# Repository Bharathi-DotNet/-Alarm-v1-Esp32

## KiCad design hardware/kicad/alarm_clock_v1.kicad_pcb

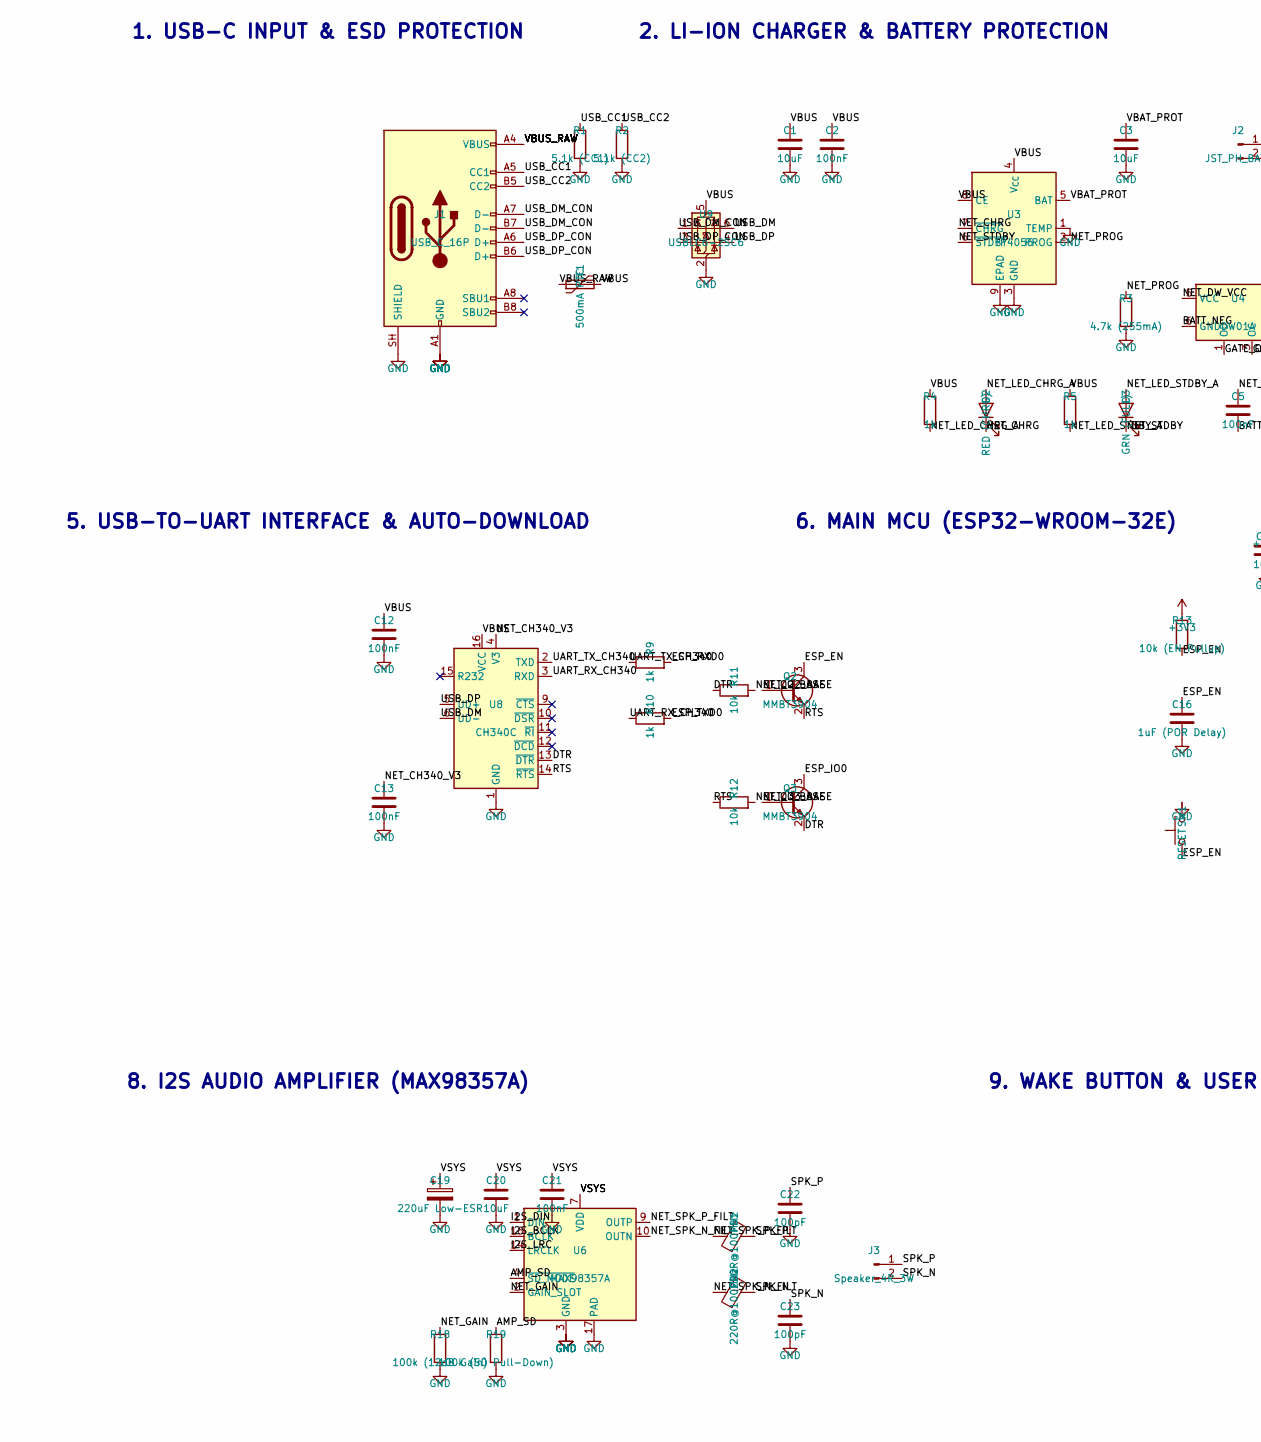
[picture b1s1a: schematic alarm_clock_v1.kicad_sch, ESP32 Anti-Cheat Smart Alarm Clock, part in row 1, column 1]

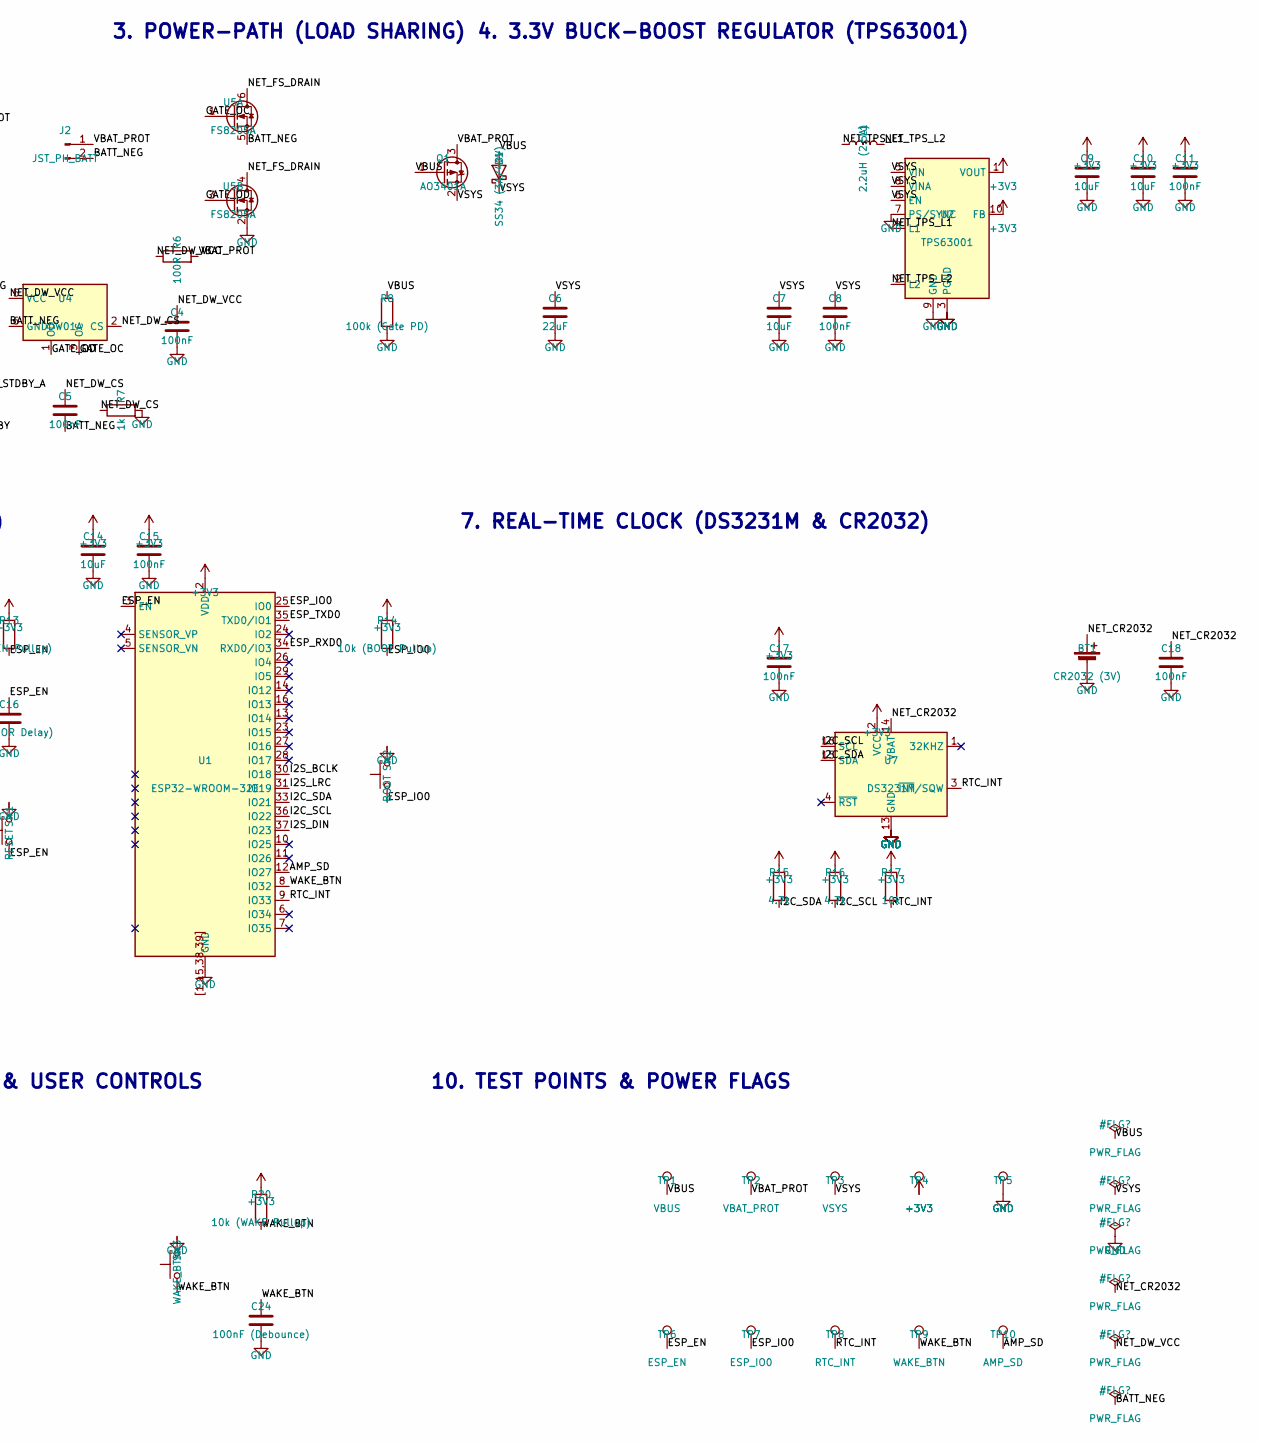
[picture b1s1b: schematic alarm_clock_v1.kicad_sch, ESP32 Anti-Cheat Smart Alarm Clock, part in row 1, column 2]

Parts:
BT1: CR2032 (3V); BatteryHolder_Keystone_1060_1x2032
C1, C3, C7, C9, C10, C14, C20: 10uF; C_0805_2012Metric
C2, C4, C5, C8, C11, C12, C13, C15, C17, C18, C21: 100nF; C_0603_1608Metric
C6: 22uF; C_0805_2012Metric
C16: 1uF (POR Delay); C_0603_1608Metric
C19: 220uF Low-ESR; CP_EIA-7343-31_Kemet-D
C22, C23: 100pF; C_0603_1608Metric
C24: 100nF (Debounce); C_0603_1608Metric
D1: SS34 (3A/40V); D_SOD-123
D2: RED (CHRG); LED_0603_1608Metric
D3: GRN (FULL); LED_0603_1608Metric
F1: 500mA PTC; Fuse_1812_4532Metric
FB1, FB2: 220R@100MHz; L_0603_1608Metric
J1: USB_C_16P; USB_C_Receptacle_HRO_TYPE-C-31-M-12
J2: JST_PH_BATT; JST_PH_B2B-PH-K_1x02_P2.00mm_Vertical
J3: Speaker_4R_3W; JST_PH_B2B-PH-K_1x02_P2.00mm_Vertical
L1: 2.2uH (2.5A); L_1210_3225Metric
Q1: AO3401A; SOT-23
Q2, Q3: MMBT3904; SOT-23
R1: 5.1k (CC1); R_0603_1608Metric
R2: 5.1k (CC2); R_0603_1608Metric
R3: 4.7k (255mA); R_0603_1608Metric
R4, R5, R7, R9, R10: 1k; R_0603_1608Metric
R6: 100R; R_0603_1608Metric
R8: 100k (Gate PD); R_0603_1608Metric
R11, R12, R17: 10k; R_0603_1608Metric
R13: 10k (EN Pullup); R_0603_1608Metric
R14: 10k (BOOT Pullup); R_0603_1608Metric
R15, R16: 4.7k; R_0603_1608Metric
R18: 100k (12dB Gain); R_0603_1608Metric
R19: 100k (SD Pull-Down); R_0603_1608Metric
R20: 10k (WAKE Pullup); R_0603_1608Metric
SW1: RESET; SW_Push_1TS009xxxx-xxxx-xxxx_6x6x5mm
SW2: BOOT; SW_Push_1TS009xxxx-xxxx-xxxx_6x6x5mm
SW3: WAKE_BTN; SW_Push_1TS009xxxx-xxxx-xxxx_6x6x5mm
TP1: VBUS; TestPoint_Pad_D1.0mm
TP2: VBAT_PROT; TestPoint_Pad_D1.0mm
TP3: VSYS; TestPoint_Pad_D1.0mm
TP4: +3V3; TestPoint_Pad_D1.0mm
TP5: GND; TestPoint_Pad_D1.0mm
TP6: ESP_EN; TestPoint_Pad_D1.0mm
TP7: ESP_IO0; TestPoint_Pad_D1.0mm
TP8: RTC_INT; TestPoint_Pad_D1.0mm
TP9: WAKE_BTN; TestPoint_Pad_D1.0mm
TP10: AMP_SD; TestPoint_Pad_D1.0mm
U1: ESP32-WROOM-32E
U2: TPS63001; Texas_DRC0010J_ThermalVias
U3: TP4056; SOIC-8-1EP_3.9x4.9mm_P1.27mm_EP2.41x3.3mm_ThermalVias
U4: DW01A; SOT-23-6
U5: FS8205A; TSSOP-8_4.4x3mm_P0.65mm
U6: MAX98357A; TQFN-16-1EP_3x3mm_P0.5mm_EP1.6x1.6mm
U7: DS3231M; SOIC-16W_7.5x10.3mm_P1.27mm
U8: CH340C; SOIC-16_3.9x9.9mm_P1.27mm
U9: USBLC6-2SC6; SOT-23-6

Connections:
+3V3: C9.1, C10.1, C11.1, C14.1, C15.1, C17.1, R13.1, R14.1, R15.1, R16.1, R17.1, R20.1, TP4.1, U1.2 (VDD), U2.1 (VOUT), U2.10 (FB), U7.2 (VCC)
/AMP_SD: R19.1, TP10.1, U1.12 (IO27), U6.4 (~SD_MODE)
/BATT_NEG: C5.2, J2.2, U4.6 (GND), U5.5 (S)
/DTR: Q3.2 (E), R11.1, U8.13 (~DTR)
/ESP_EN: C16.1, Q2.3 (C), R13.2, SW1.1, TP6.1, U1.3 (EN)
/ESP_IO0: Q3.3 (C), R14.2, SW2.1, TP7.1, U1.25 (IO0)
/ESP_RXD0: R9.2, U1.34 (RXD0/IO3)
/ESP_TXD0: R10.2, U1.35 (TXD0/IO1)
/GATE_OC: U4.3 (OC), U5.1 (G)
/GATE_OD: U4.1 (OD), U5.3 (G)
/I2C_SCL: R16.2, U1.36 (IO22), U7.16 (SCL)
/I2C_SDA: R15.2, U1.33 (IO21), U7.15 (SDA)
/I2S_BCLK: U1.30 (IO18), U6.16 (BCLK)
/I2S_DIN: U1.37 (IO23), U6.1 (DIN)
/I2S_LRC: U1.31 (IO19), U6.14 (LRCLK)
/NET_CH340_V3: C13.1, U8.4 (V3)
/NET_CHRG: D2.1 (K), U3.7 (~CHRG)
/NET_CR2032: BT1.1 (+), C18.1, U7.14 (VBAT)
/NET_DW_CS: C5.1, R7.1, U4.2 (CS)
/NET_DW_VCC: C4.1, R6.1, U4.5 (VCC)
/NET_FS_DRAIN: U5.4 (D), U5.6 (D)
/NET_GAIN: R18.1, U6.2 (GAIN_SLOT)
/NET_LED_CHRG_A: D2.2 (A), R4.2
/NET_LED_STDBY_A: D3.2 (A), R5.2
/NET_PROG: R3.1, U3.2 (PROG)
/NET_Q2_BASE: Q2.1 (B), R11.2
/NET_Q3_BASE: Q3.1 (B), R12.2
/NET_SPK_N_FILT: FB2.1, U6.10 (OUTN)
/NET_SPK_P_FILT: FB1.1, U6.9 (OUTP)
/NET_STDBY: D3.1 (K), U3.6 (~STDBY)
/NET_TPS_L1: L1.1, U2.4 (L1)
/NET_TPS_L2: L1.2, U2.2 (L2)
/RTC_INT: R17.2, TP8.1, U1.9 (IO33), U7.3 (~INT/SQW)
/RTS: Q2.2 (E), R12.1, U8.14 (~RTS)
/SPK_N: C23.1, FB2.2, J3.2
/SPK_P: C22.1, FB1.2, J3.1
/UART_RX_CH340: R10.1, U8.3 (RXD)
/UART_TX_CH340: R9.1, U8.2 (TXD)
/USB_CC1: J1.A5 (CC1), R1.1
/USB_CC2: J1.B5 (CC2), R2.1
/USB_DM: U8.6 (UD-), U9.6 (I/O1)
/USB_DM_CON: J1.A7 (D-), J1.B7 (D-), U9.1 (I/O1)
/USB_DP: U8.5 (UD+), U9.4 (I/O2)
/USB_DP_CON: J1.A6 (D+), J1.B6 (D+), U9.3 (I/O2)
/VBAT_PROT: C3.1, J2.1, Q1.3 (D), R6.2, TP2.1, U3.5 (BAT)
/VBUS: C1.1, C2.1, C12.1, D1.2 (A), F1.2, Q1.1 (G), R4.1, R5.1, R8.1, TP1.1, U3.4 (V_{CC}), U3.8 (CE), U8.16 (VCC), U9.5 (VBUS)
/VBUS_RAW: F1.1, J1.A4 (VBUS), J1.A9 (VBUS), J1.B4 (VBUS), J1.B9 (VBUS)
/VSYS: C6.1, C7.1, C8.1, C19.1, C20.1, C21.1, D1.1 (K), Q1.2 (S), TP3.1, U2.5 (VIN), U2.6 (EN), U2.8 (VINA), U6.7 (VDD), U6.8 (VDD)
/WAKE_BTN: C24.1, R20.2, SW3.1, TP9.1, U1.8 (IO32)
GND: BT1.2 (-), C1.2, C2.2, C3.2, C4.2, C6.2, C7.2, C8.2, C9.2, C10.2, C11.2, C12.2, C13.2, C14.2, C15.2, C16.2, C17.2, C18.2, C19.2, C20.2, C21.2, C22.2, C23.2, C24.2, J1.A1 (GND), J1.A12 (GND), J1.B1 (GND), J1.B12 (GND), J1.SH (SHIELD), R1.2, R2.2, R3.2, R7.2, R8.2, R18.2, R19.2, SW1.2, SW2.2, SW3.2, TP5.1, U1.1, U1.15, U1.38, U1.39, U1.[1,15,38,39] (GND), U2.3 (PGND), U2.7 (PS/SYNC), U2.9 (GND), U2.11 (PGND), U3.1 (TEMP), U3.3 (GND), U3.9 (EPAD), U5.2 (S), U6.3 (GND), U6.11 (GND), U6.15 (GND), U6.17 (PAD), U7.5 (GND), U7.6 (GND), U7.7 (GND), U7.8 (GND), U7.9 (GND), U7.10 (GND), U7.11 (GND), U7.12 (GND), U7.13 (GND), U8.1 (GND), U9.2 (GND)

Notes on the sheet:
1. USB-C INPUT & ESD PROTECTION
2. LI-ION CHARGER & BATTERY PROTECTION
3. POWER-PATH (LOAD SHARING)
4. 3.3V BUCK-BOOST REGULATOR (TPS63001)
5. USB-TO-UART INTERFACE & AUTO-DOWNLOAD
6. MAIN MCU (ESP32-WROOM-32E)
7. REAL-TIME CLOCK (DS3231M & CR2032)
8. I2S AUDIO AMPLIFIER (MAX98357A)
9. WAKE BUTTON & USER CONTROLS
10. TEST POINTS & POWER FLAGS

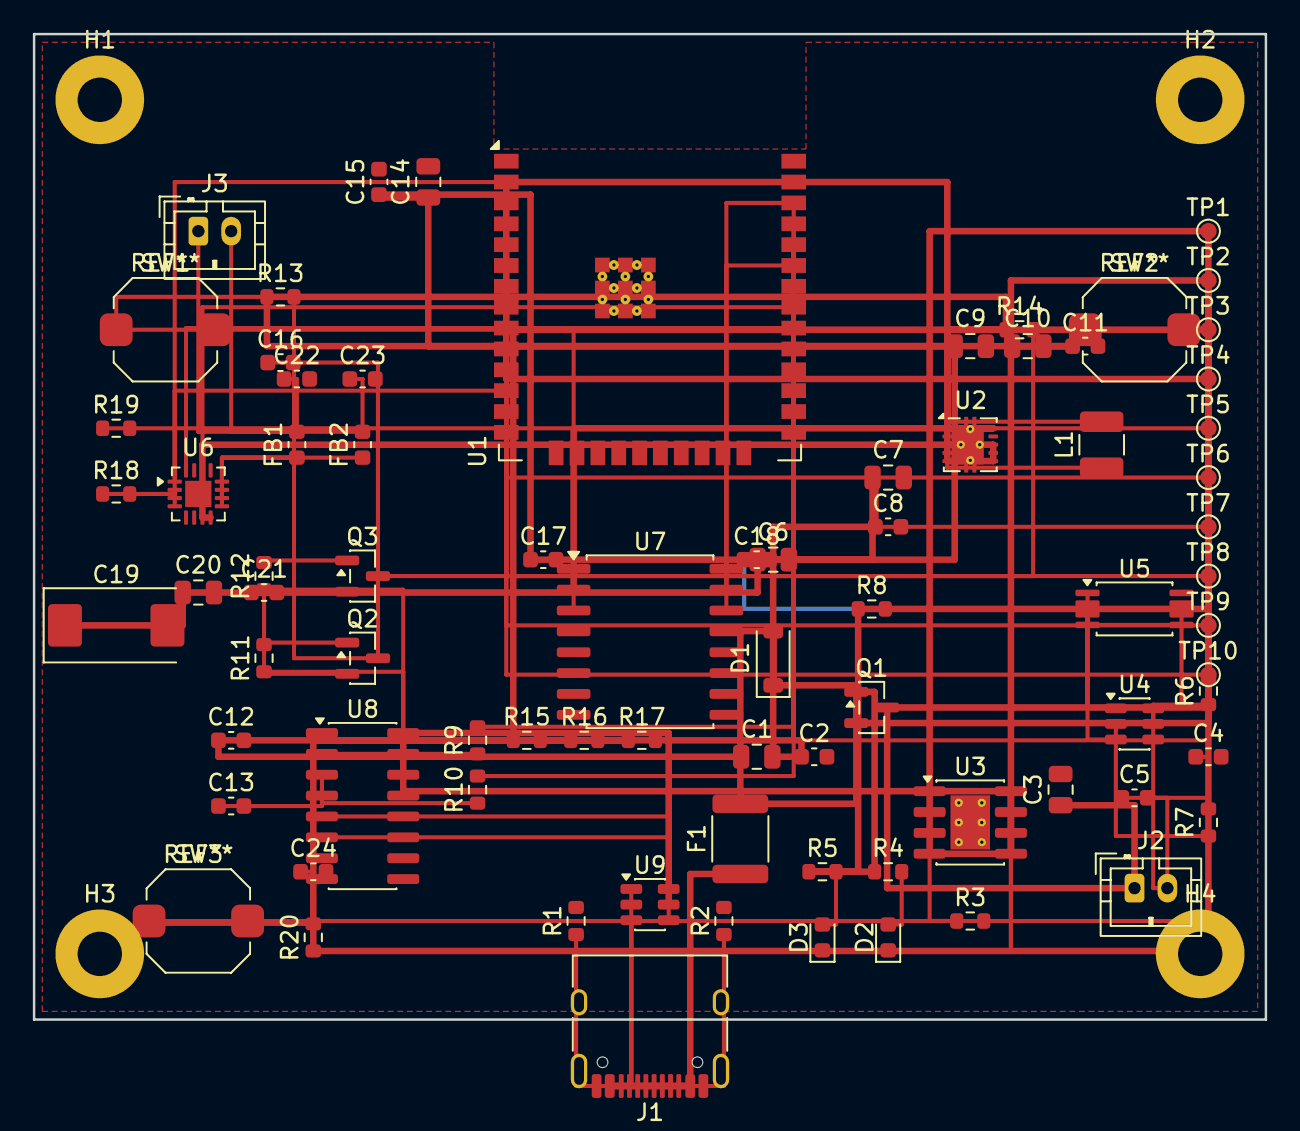
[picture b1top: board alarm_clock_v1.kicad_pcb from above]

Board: 2 copper layers, 75.0 x 60.0 mm, 84 parts (1 on the bottom side), 50 nets.

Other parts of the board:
H1, H2, H3, H4: MountingHole_2.7mm_M2.5_Pad

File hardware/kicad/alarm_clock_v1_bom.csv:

"Refs","Value","Footprint","Qty","DNP"
"BT1","CR2032 (3V)","Battery:BatteryHolder_Keystone_1060_1x2032","1",""
"C1","10uF","Capacitor_SMD:C_0805_2012Metric","1",""
"C2","100nF","Capacitor_SMD:C_0603_1608Metric","1",""
"C3","10uF","Capacitor_SMD:C_0805_2012Metric","1",""
"C4","100nF","Capacitor_SMD:C_0603_1608Metric","1",""
"C5","100nF","Capacitor_SMD:C_0603_1608Metric","1",""
"C6","22uF","Capacitor_SMD:C_0805_2012Metric","1",""
"C7","10uF","Capacitor_SMD:C_0805_2012Metric","1",""
"C8","100nF","Capacitor_SMD:C_0603_1608Metric","1",""
"C9","10uF","Capacitor_SMD:C_0805_2012Metric","1",""
"C10","10uF","Capacitor_SMD:C_0805_2012Metric","1",""
"C11","100nF","Capacitor_SMD:C_0603_1608Metric","1",""
"C12","100nF","Capacitor_SMD:C_0603_1608Metric","1",""
"C13","100nF","Capacitor_SMD:C_0603_1608Metric","1",""
"C14","10uF","Capacitor_SMD:C_0805_2012Metric","1",""
"C15","100nF","Capacitor_SMD:C_0603_1608Metric","1",""
"C16","1uF (POR Delay)","Capacitor_SMD:C_0603_1608Metric","1",""
"C17","100nF","Capacitor_SMD:C_0603_1608Metric","1",""
"C18","100nF","Capacitor_SMD:C_0603_1608Metric","1",""
"C19","220uF Low-ESR","Capacitor_Tantalum_SMD:CP_EIA-7343-31_Kemet-D","1",""
"C20","10uF","Capacitor_SMD:C_0805_2012Metric","1",""
"C21","100nF","Capacitor_SMD:C_0603_1608Metric","1",""
"C22","100pF","Capacitor_SMD:C_0603_1608Metric","1",""
"C23","100pF","Capacitor_SMD:C_0603_1608Metric","1",""
"C24","100nF (Debounce)","Capacitor_SMD:C_0603_1608Metric","1",""
"D1","SS34 (3A/40V)","Diode_SMD:D_SOD-123","1",""
"D2","RED (CHRG)","LED_SMD:LED_0603_1608Metric","1",""
"D3","GRN (FULL)","LED_SMD:LED_0603_1608Metric","1",""
"F1","500mA PTC","Fuse:Fuse_1812_4532Metric","1",""
"FB1","220R@100MHz","Inductor_SMD:L_0603_1608Metric","1",""
"FB2","220R@100MHz","Inductor_SMD:L_0603_1608Metric","1",""
"J1","USB_C_16P","Connector_USB:USB_C_Receptacle_HRO_TYPE-C-31-M-12","1",""
"J2","JST_PH_BATT","Connector_JST:JST_PH_B2B-PH-K_1x02_P2.00mm_Vertical","1",""
"J3","Speaker_4R_3W","Connector_JST:JST_PH_B2B-PH-K_1x02_P2.00mm_Vertical","1",""
"L1","2.2uH (2.5A)","Inductor_SMD:L_1210_3225Metric","1",""
"Q1","AO3401A","Package_TO_SOT_SMD:SOT-23","1",""
"Q2","MMBT3904","Package_TO_SOT_SMD:SOT-23","1",""
"Q3","MMBT3904","Package_TO_SOT_SMD:SOT-23","1",""
"R1","5.1k (CC1)","Resistor_SMD:R_0603_1608Metric","1",""
"R2","5.1k (CC2)","Resistor_SMD:R_0603_1608Metric","1",""
"R3","4.7k (255mA)","Resistor_SMD:R_0603_1608Metric","1",""
"R4","1k","Resistor_SMD:R_0603_1608Metric","1",""
"R5","1k","Resistor_SMD:R_0603_1608Metric","1",""
"R6","100R","Resistor_SMD:R_0603_1608Metric","1",""
"R7","1k","Resistor_SMD:R_0603_1608Metric","1",""
"R8","100k (Gate PD)","Resistor_SMD:R_0603_1608Metric","1",""
"R9","1k","Resistor_SMD:R_0603_1608Metric","1",""
"R10","1k","Resistor_SMD:R_0603_1608Metric","1",""
"R11","10k","Resistor_SMD:R_0603_1608Metric","1",""
"R12","10k","Resistor_SMD:R_0603_1608Metric","1",""
"R13","10k (EN Pullup)","Resistor_SMD:R_0603_1608Metric","1",""
"R14","10k (BOOT Pullup)","Resistor_SMD:R_0603_1608Metric","1",""
"R15","4.7k","Resistor_SMD:R_0603_1608Metric","1",""
"R16","4.7k","Resistor_SMD:R_0603_1608Metric","1",""
"R17","10k","Resistor_SMD:R_0603_1608Metric","1",""
"R18","100k (12dB Gain)","Resistor_SMD:R_0603_1608Metric","1",""
"R19","100k (SD Pull-Down)","Resistor_SMD:R_0603_1608Metric","1",""
"R20","10k (WAKE Pullup)","Resistor_SMD:R_0603_1608Metric","1",""
"SW1","RESET","Button_Switch_SMD:SW_Push_1TS009xxxx-xxxx-xxxx_6x6x5mm","1",""
"SW2","BOOT","Button_Switch_SMD:SW_Push_1TS009xxxx-xxxx-xxxx_6x6x5mm","1",""
"SW3","WAKE_BTN","Button_Switch_SMD:SW_Push_1TS009xxxx-xxxx-xxxx_6x6x5mm","1",""
"TP1","VBUS","TestPoint:TestPoint_Pad_D1.0mm","1",""
"TP2","VBAT_PROT","TestPoint:TestPoint_Pad_D1.0mm","1",""
"TP3","VSYS","TestPoint:TestPoint_Pad_D1.0mm","1",""
"TP4","+3V3","TestPoint:TestPoint_Pad_D1.0mm","1",""
"TP5","GND","TestPoint:TestPoint_Pad_D1.0mm","1",""
"TP6","ESP_EN","TestPoint:TestPoint_Pad_D1.0mm","1",""
"TP7","ESP_IO0","TestPoint:TestPoint_Pad_D1.0mm","1",""
"TP8","RTC_INT","TestPoint:TestPoint_Pad_D1.0mm","1",""
"TP9","WAKE_BTN","TestPoint:TestPoint_Pad_D1.0mm","1",""
"TP10","AMP_SD","TestPoint:TestPoint_Pad_D1.0mm","1",""
"U1","ESP32-WROOM-32E","RF_Module:ESP32-WROOM-32E","1",""
"U2","TPS63001","Package_SON:Texas_DRC0010J_ThermalVias","1",""
"U3","TP4056","Package_SO:SOIC-8-1EP_3.9x4.9mm_P1.27mm_EP2.41x3.3mm_ThermalVias","1",""
"U4","DW01A","Package_TO_SOT_SMD:SOT-23-6","1",""
"U5","FS8205A","Package_SO:TSSOP-8_4.4x3mm_P0.65mm","1",""
"U6","MAX98357A","Package_DFN_QFN:TQFN-16-1EP_3x3mm_P0.5mm_EP1.6x1.6mm","1",""
"U7","DS3231M","Package_SO:SOIC-16W_7.5x10.3mm_P1.27mm","1",""
"U8","CH340C","Package_SO:SOIC-16_3.9x9.9mm_P1.27mm","1",""
"U9","USBLC6-2SC6","Package_TO_SOT_SMD:SOT-23-6","1",""

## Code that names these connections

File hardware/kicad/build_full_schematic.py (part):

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                     "Connector_USB:USB_C_Receptacle_HRO_TYPE-C-31-M-12", 50, 60, rot=0)
    # VBUS pins: A4, A9, B4, B9
    for p in ["A4", "A9", "B4", "B9"]:
        gen.connect_pin(j1, p, "VBUS_RAW")
    # GND pins: A1, A12, B1, B12, SH
    for p in ["A1", "A12", "B1", "B12", "SH"]:
        gen.connect_pin(j1, p, "GND")
    # CC pins
    gen.connect_pin(j1, "A5", "USB_CC1")
    gen.connect_pin(j1, "B5", "USB_CC2")
    # Data pins
    gen.connect_pin(j1, "A6", "USB_DP_CON")
    gen.connect_pin(j1, "B6", "USB_DP_CON")
    gen.connect_pin(j1, "A7", "USB_DM_CON")
    gen.connect_pin(j1, "B7", "USB_DM_CON")
    # SBU pins (NC)
    gen.nc_pin(j1, "A8")
    gen.nc_pin(j1, "B8")

    # CC Pull-downs
    r_cc1 = gen.add_sym("Device:R", "R_CC1", "5.1k", "Resistor_SMD:R_0603_1608Metric", 75, 45, rot=0)
    gen.connect_pin(r_cc1, "1", "USB_CC1")
    gen.connect_pin(r_cc1, "2", "GND")

    r_cc2 = gen.add_sym("Device:R", "R_CC2", "5.1k", "Resistor_SMD:R_0603_1608Metric", 85, 45, rot=0)
    gen.connect_pin(r_cc2, "1", "USB_CC2")
    gen.connect_pin(r_cc2, "2", "GND")

    # F1: Polyfuse PTC on VBUS
    f1 = gen.add_sym("Device:Polyfuse", "F1", "500mA", "Fuse:Fuse_1812_4532Metric", 75, 70, rot=90)
    gen.connect_pin(f1, "1", "VBUS_RAW")
    gen.connect_pin(f1, "2", "VBUS")

    # U9: USBLC6-2SC6 ESD Protection
    u9 = gen.add_sym("Power_Protection:USBLC6-2P6", "U9", "USBLC6-2SC6", "Package_TO_SOT_SMD:SOT-23-6", 100, 60, rot=0)
    gen.connect_pin(u9, "1", "USB_DM_CON")
    gen.connect_pin(u9, "2", "GND")
    gen.connect_pin(u9, "3", "USB_DP_CON")
    gen.connect_pin(u9, "4", "USB_DP")
    gen.connect_pin(u9, "5", "VBUS")
    gen.connect_pin(u9, "6", "USB_DM")

    # VBUS Filter Caps
    c_vbus1 = gen.add_sym("Device:C", "C_VBUS1", "10uF", "Capacitor_SMD:C_0805_2012Metric", 115, 45, rot=0)
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    gen.connect_pin(u3, "2", "NET_PROG")
    gen.connect_pin(u3, "3", "GND")
    gen.connect_pin(u3, "4", "VBUS")
    gen.connect_pin(u3, "5", "VBAT_PROT")
    gen.connect_pin(u3, "6", "NET_STDBY")
    gen.connect_pin(u3, "7", "NET_CHRG")
    gen.connect_pin(u3, "8", "VBUS")
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    # J2: Battery Connector (JST-PH 2.0mm)
    j2 = gen.add_sym("Connector:Conn_01x02_Pin", "J2", "JST_PH_BATT",
                     "Connector_JST:JST_PH_B2B-PH-K_1x02_P2.00mm_Vertical", 195, 45, rot=0)
    gen.connect_pin(j2, "1", "VBAT_PROT")
    gen.connect_pin(j2, "2", "BATT_NEG")

    # Battery Protection IC U4: DW01A
    u4 = gen.add_sym("Battery_Management:DW01A", "U4", "DW01A", "Package_TO_SOT_SMD:SOT-23-6", 195, 75, rot=0)
    gen.connect_pin(u4, "1", "GATE_OD")
    gen.connect_pin(u4, "2", "NET_DW_CS")
    gen.connect_pin(u4, "3", "GATE_OC")
    gen.connect_pin(u4, "4", "NET_DW_VCC")
    gen.connect_pin(u4, "5", "BATT_NEG")
    gen.nc_pin(u4, "6") # TD

    r_dw_vcc = gen.add_sym("Device:R", "R_VDD", "100R", "Resistor_SMD:R_0603_1608Metric", 215, 65, rot=90)
    gen.connect_pin(r_dw_vcc, "1", "NET_DW_VCC")
    gen.connect_pin(r_dw_vcc, "2", "VBAT_PROT")

    c_dw_vcc = gen.add_sym("Device:C", "C_VDD", "100nF", "Capacitor_SMD:C_0603_1608Metric", 215, 80, rot=0)
    gen.connect_pin(c_dw_vcc, "1", "NET_DW_VCC")
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
    c_dw_cs = gen.add_sym("Device:C", "C_CS", "100nF", "Capacitor_SMD:C_0603_1608Metric", 195, 95, rot=0)
    gen.connect_pin(c_dw_cs, "1", "NET_DW_CS")
    gen.connect_pin(c_dw_cs, "2", "BATT_NEG")

    # Protection MOSFET U5: FS8205A Dual N-FET
    u5 = gen.add_sym("Transistor_FET:Q_Dual_NMOS_G1S2G2D2S1D1", "U5", "FS8205A",
                     "Package_SO:TSSOP-8_4.4x3mm_P0.65mm", 220, 45, rot=0)
    gen.connect_pin(u5, "1", "GATE_OC")
    gen.connect_pin(u5, "2", "GND")
    gen.connect_pin(u5, "3", "GATE_OD")
    gen.connect_pin(u5, "4", "NET_FS_DRAIN")
    gen.connect_pin(u5, "5", "BATT_NEG")
    gen.connect_pin(u5, "6", "NET_FS_DRAIN")

    # Output / decoupling caps for battery
    c_chg_out = gen.add_sym("Device:C", "C_CHG_OUT", "10uF", "Capacitor_SMD:C_0805_2012Metric", 175, 45, rot=0)
    gen.connect_pin(c_chg_out, "1", "VBAT_PROT")
    gen.connect_pin(c_chg_out, "2", "GND")

    # =========================================================================
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    # Q1: AO3401A P-MOSFET
    q1 = gen.add_sym("Transistor_FET:TP0610T", "Q1", "AO3401A", "Package_TO_SOT_SMD:SOT-23", 260, 50, rot=0)
    gen.connect_pin(q1, "1", "VBUS")      # Gate to VBUS
    gen.connect_pin(q1, "2", "VSYS")      # Source to VSYS
    gen.connect_pin(q1, "3", "VBAT_PROT") # Drain to Battery

    r_gate = gen.add_sym("Device:R", "R_GATE", "100k", "Resistor_SMD:R_0603_1608Metric", 250, 75, rot=0)
    gen.connect_pin(r_gate, "1", "VBUS")
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    # D1: SS34 Schottky Diode
    d1 = gen.add_sym("Device:D_Schottky", "D1", "SS34 (3A/40V)", "Diode_SMD:D_SOD-123", 275, 50, rot=90)
    gen.connect_pin(d1, "2", "VBUS") # Anode (pin 2 in KiCad)
    gen.connect_pin(d1, "1", "VSYS") # Cathode (pin 1 in KiCad)

    c_sys = gen.add_sym("Device:C", "C_SYS", "22uF", "Capacitor_SMD:C_0805_2012Metric", 285, 75, rot=0)
    gen.connect_pin(c_sys, "1", "VSYS")
    gen.connect_pin(c_sys, "2", "GND")

    # =========================================================================
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    u2 = gen.add_sym("Regulator_Switching:TPS63000", "U2", "TPS63001",
                     "Package_SON:Texas_DRC0010J_ThermalVias", 355, 60, rot=0)
    gen.connect_pin(u2, "1", "+3V3")     # VOUT
    gen.connect_pin(u2, "2", "VSYS")     # VINA
    gen.connect_pin(u2, "3", "GND")      # GND
    gen.connect_pin(u2, "4", "GND")      # PS/SYNC to GND (Power-Save Mode 30uA Iq)
    gen.connect_pin(u2, "5", "NET_TPS_L1")
    gen.connect_pin(u2, "6", "VSYS")     # VIN
    gen.connect_pin(u2, "7", "VSYS")     # EN
    gen.connect_pin(u2, "8", "NET_TPS_L2")
    gen.connect_pin(u2, "9", "GND")      # PGND
    gen.connect_pin(u2, "10", "+3V3")    # FB (Fixed 3.3V connects directly to VOUT)
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
    # Input Capacitors
    c_in1 = gen.add_sym("Device:C", "C_IN1", "10uF", "Capacitor_SMD:C_0805_2012Metric", 325, 75, rot=0)
    gen.connect_pin(c_in1, "1", "VSYS")
    gen.connect_pin(c_in1, "2", "GND")

    c_in2 = gen.add_sym("Device:C", "C_IN2", "100nF", "Capacitor_SMD:C_0603_1608Metric", 335, 75, rot=0)
    gen.connect_pin(c_in2, "1", "VSYS")
    gen.connect_pin(c_in2, "2", "GND")

    # Output Capacitors
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    # =========================================================================
    u8 = gen.add_sym("Interface_USB:CH340C", "U8", "CH340C", "Package_SO:SOIC-16_3.9x9.9mm_P1.27mm", 60, 150, rot=0)
    gen.connect_pin(u8, "1", "GND")
    gen.connect_pin(u8, "2", "UART_TX_CH340")
    gen.connect_pin(u8, "3", "UART_RX_CH340")
    gen.connect_pin(u8, "4", "NET_CH340_V3")
    gen.connect_pin(u8, "5", "USB_DP")
    gen.connect_pin(u8, "6", "USB_DM")
    gen.nc_pin(u8, "7") # XI
    gen.nc_pin(u8, "8") # XO
    gen.nc_pin(u8, "9") # CTS
    gen.nc_pin(u8, "10") # DSR
    gen.nc_pin(u8, "11") # RI
    gen.nc_pin(u8, "12") # DCD
    gen.connect_pin(u8, "13", "DTR")
    gen.connect_pin(u8, "14", "RTS")
    gen.nc_pin(u8, "15") # R232
    gen.connect_pin(u8, "16", "VBUS") # Powered STRICTLY from VBUS

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
    # Series 1k isolation resistors (prevent phantom back-powering CH340C when USB is unplugged)
    r_tx = gen.add_sym("Device:R", "R_TX", "1k", "Resistor_SMD:R_0603_1608Metric", 90, 140, rot=90)
    gen.connect_pin(r_tx, "1", "UART_TX_CH340")
    gen.connect_pin(r_tx, "2", "ESP_RXD0")

    r_rx = gen.add_sym("Device:R", "R_RX", "1k", "Resistor_SMD:R_0603_1608Metric", 90, 150, rot=90)
    gen.connect_pin(r_rx, "1", "UART_RX_CH340")
    gen.connect_pin(r_rx, "2", "ESP_TXD0")

    # Auto-Reset / Download Transistors (MMBT3904)
    # Q2: Reset Control
    q2 = gen.add_sym("Transistor_BJT:Q_NPN_BEC", "Q2", "MMBT3904", "Package_TO_SOT_SMD:SOT-23", 115, 145, rot=0)
    gen.connect_pin(q2, "1", "NET_Q2_BASE")
    gen.connect_pin(q2, "2", "RTS")
    gen.connect_pin(q2, "3", "ESP_EN")

    r_dtr = gen.add_sym("Device:R", "R_DTR", "10k", "Resistor_SMD:R_0603_1608Metric", 105, 145, rot=90)
    gen.connect_pin(r_dtr, "1", "DTR")
    gen.connect_pin(r_dtr, "2", "NET_Q2_BASE")

    # Q3: Boot Mode Control
    q3 = gen.add_sym("Transistor_BJT:Q_NPN_BEC", "Q3", "MMBT3904", "Package_TO_SOT_SMD:SOT-23", 115, 165, rot=0)
    gen.connect_pin(q3, "1", "NET_Q3_BASE")
    gen.connect_pin(q3, "2", "DTR")
    gen.connect_pin(q3, "3", "ESP_IO0")

    r_rts = gen.add_sym("Device:R", "R_RTS", "10k", "Resistor_SMD:R_0603_1608Metric", 105, 165, rot=90)
    gen.connect_pin(r_rts, "1", "RTS")
    gen.connect_pin(r_rts, "2", "NET_Q3_BASE")

    # =========================================================================
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    # =========================================================================
    u1 = gen.add_sym("RF_Module:ESP32-WROOM-32E", "U1", "ESP32-WROOM-32E", "RF_Module:ESP32-WROOM-32E", 220, 160, rot=0)
    gen.connect_pin(u1, "2", "+3V3")
    gen.connect_pin(u1, "3", "ESP_EN")
    gen.nc_pin(u1, "4") # SENSOR_VP
    gen.nc_pin(u1, "5") # SENSOR_VN
    gen.nc_pin(u1, "6") # IO34
    gen.nc_pin(u1, "7") # IO35
    gen.connect_pin(u1, "8", "WAKE_BTN")  # GPIO32 - Wake Button
    gen.connect_pin(u1, "9", "RTC_INT")   # GPIO33 - RTC Alarm Wake
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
